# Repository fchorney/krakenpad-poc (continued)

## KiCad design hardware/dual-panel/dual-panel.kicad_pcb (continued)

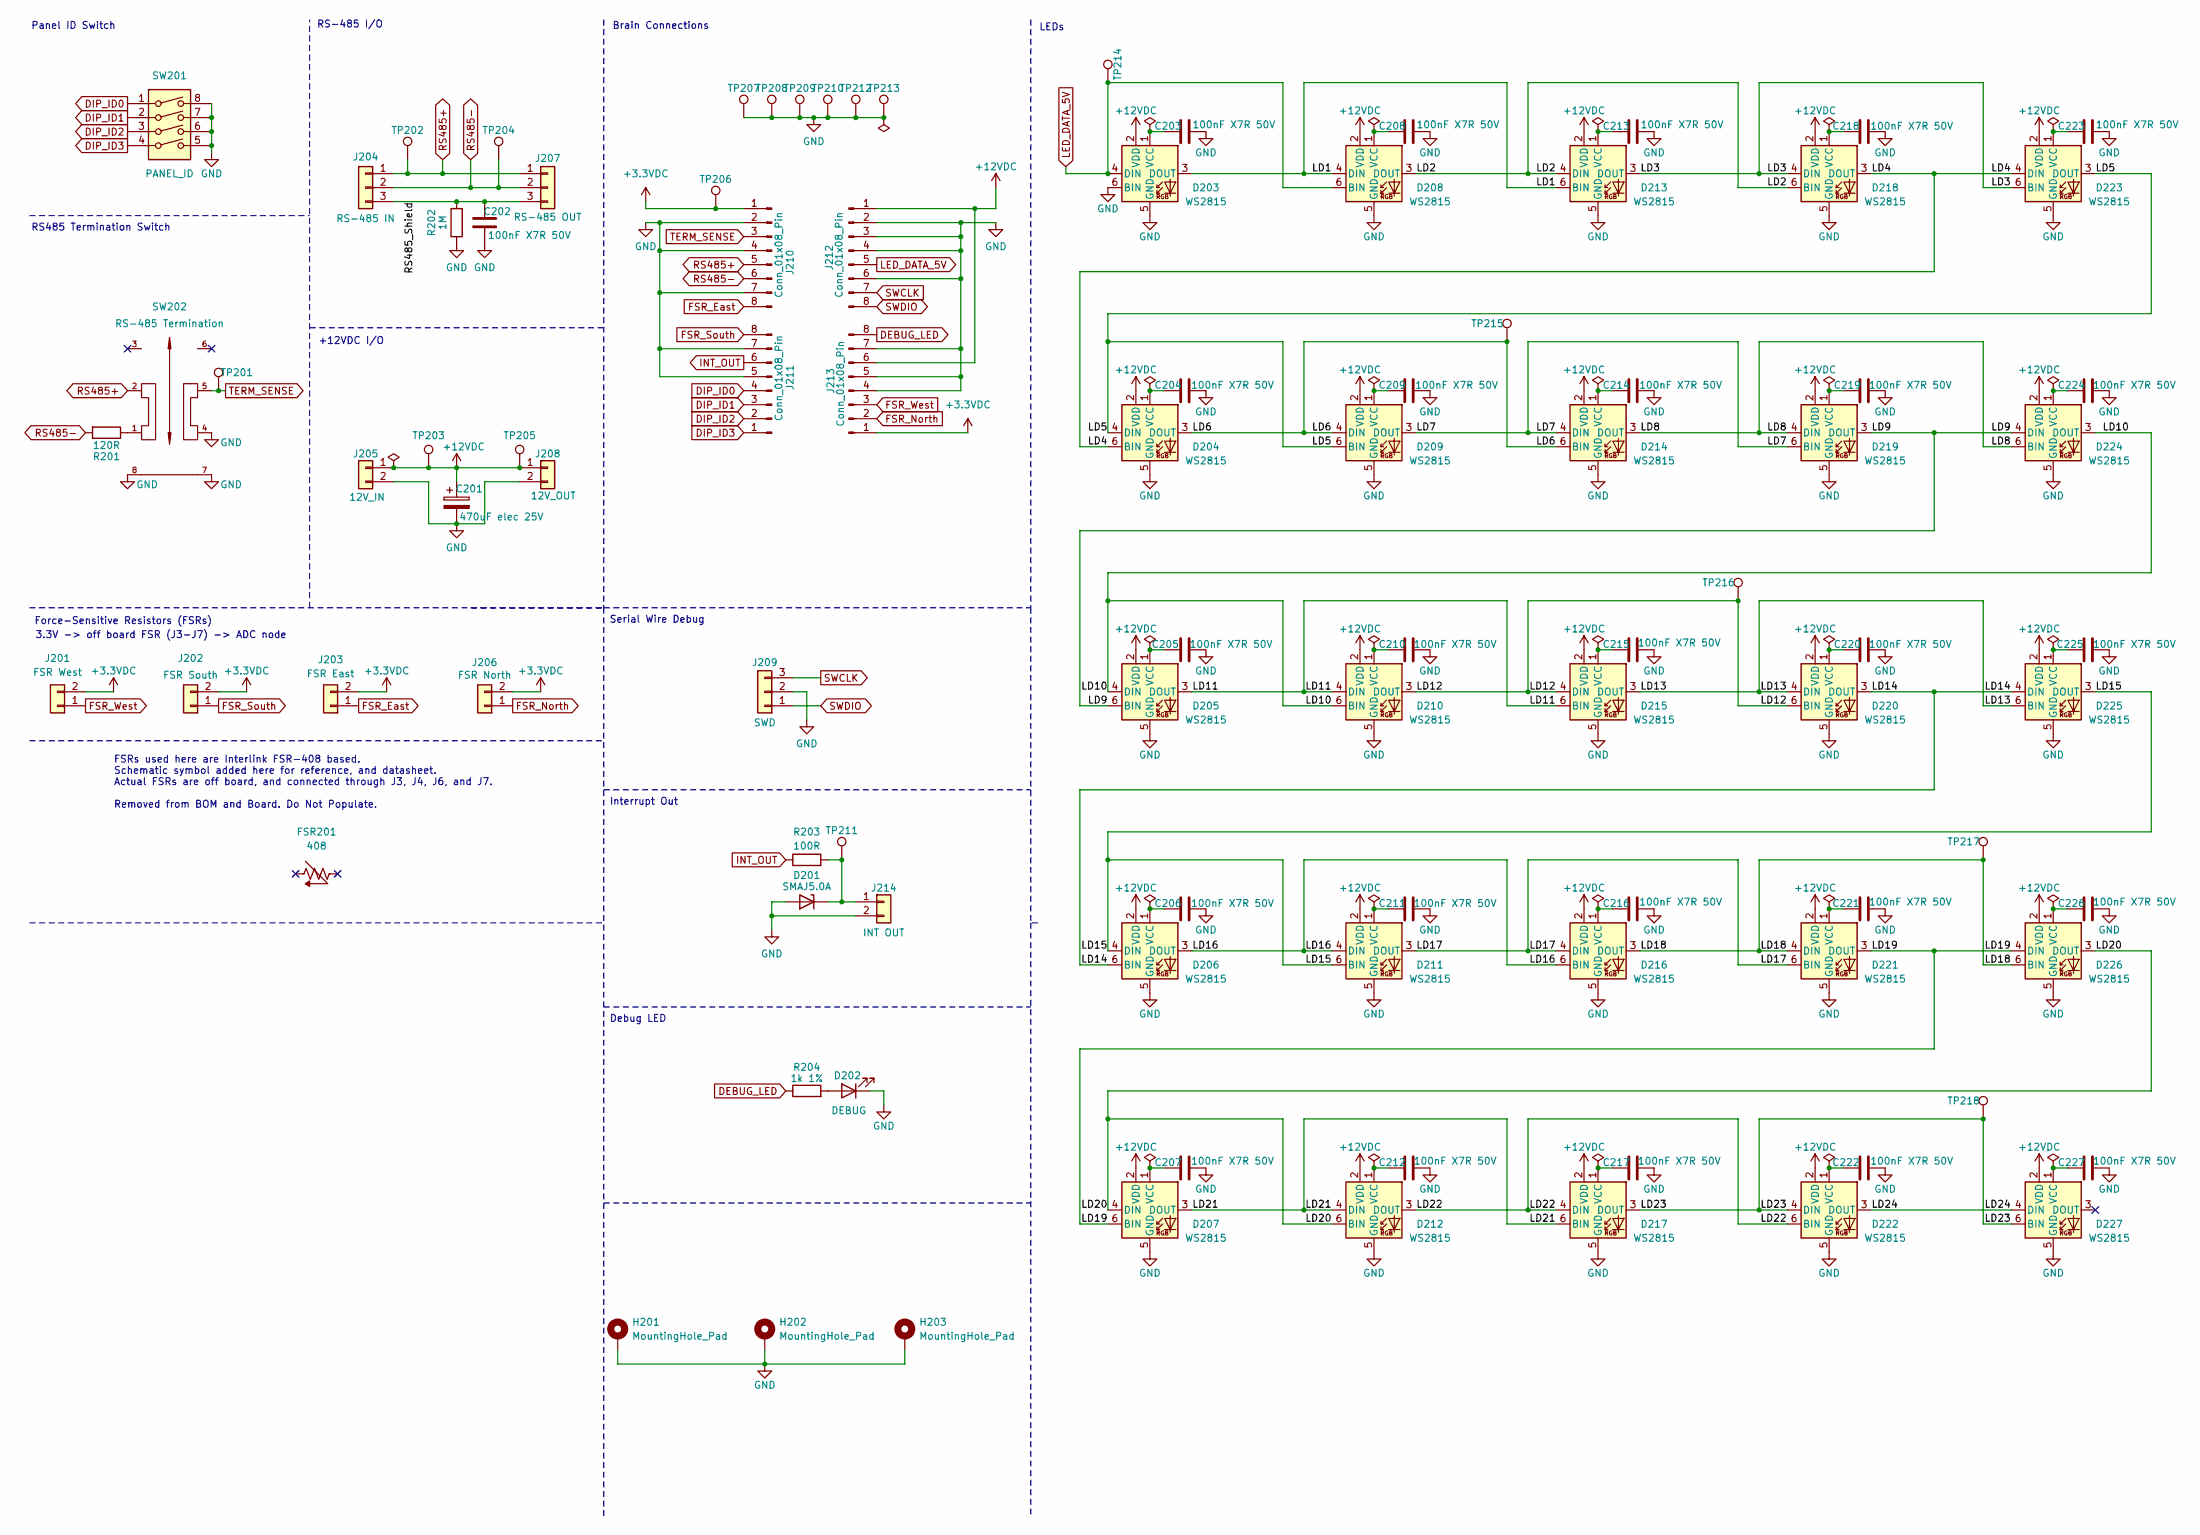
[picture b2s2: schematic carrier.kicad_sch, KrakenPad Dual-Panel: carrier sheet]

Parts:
C201: 470uF elec 25V; CP_Elec_10x10.5_RVT1E471M; MPN RVT1E471M1010; LCSC C82014
C202, C203, C204, C205, C206, C207, C208, C209, C210, C211, C212, C213, C214, C215, C216, C217, C218, C219, C220, C221, C222, C223, C224, C225, C226, C227: 100nF X7R 50V; C_0603_1608Metric; LCSC C14663
D201: SMAJ5.0A; D_SMA; MPN SMAJ5.0A; LCSC C113952
D202: DEBUG; LED_0603_1608Metric; MPN DYWH-19-21SUGC/4T; LCSC C47416536
D203, D204, D205, D206, D207, D208, D209, D210, D211, D212, D213, D214, D215, D216, D217, D218, D219, D220, D221, D222, D223, D224, D225, D226, D227: WS2815; WS2815_PLCC6_5.0x5.0mm_P1.6mm; MPN WS2815B-V1; LCSC C5446699
FSR201: 408
H201, H202, H203: MountingHole_Pad; MountingHole_3.2mm_M3_Pad
J201: FSR West; JST_PH_B2B-PH-K_1x02_P2.00mm_Vertical; MPN B2B-PH-K-S(LF)(SN); LCSC C131337
J202: FSR South; JST_PH_B2B-PH-K_1x02_P2.00mm_Vertical; MPN B2B-PH-K-S(LF)(SN); LCSC C131337
J203: FSR East; JST_PH_B2B-PH-K_1x02_P2.00mm_Vertical; MPN B2B-PH-K-S(LF)(SN); LCSC C131337
J204: RS-485 IN; Molex_Micro-Fit_3.0_43650-0300_1x03_P3.00mm_Horizontal; MPN 43650-0300; LCSC C503478
J205: 12V_IN; Molex_Micro-Fit_3.0_43650-0200_1x02_P3.00mm_Horizontal; MPN 43650-0200; LCSC C192562
J206: FSR North; JST_PH_B2B-PH-K_1x02_P2.00mm_Vertical; MPN B2B-PH-K-S(LF)(SN); LCSC C131337
J207: RS-485 OUT; Molex_Micro-Fit_3.0_43650-0300_1x03_P3.00mm_Horizontal; MPN 43650-0300; LCSC C503478
J208: 12V_OUT; Molex_Micro-Fit_3.0_43650-0200_1x02_P3.00mm_Horizontal; MPN 43650-0200; LCSC C192562
J209: SWD; PinHeader_1x03_P2.54mm_Vertical; MPN PZ254V-11-03P; LCSC C2937625
J210, J211, J212, J213: Conn_01x08_Pin; PinHeader_1x08_P2.54mm_Vertical
J214: INT OUT; TerminalBlock_WJ500V-5.08-2P; MPN WJ500V-5.08-2P; LCSC C8465
R201: 120R; R_0603_1608Metric; LCSC C22787
R202: 1M; R_0603_1608Metric; LCSC C22935
R203: 100R; R_0603_1608Metric; LCSC C22775
R204: 1k 1%; R_0603_1608Metric; LCSC C2907002
SW201: PANEL_ID; SW_DIP_SPSTx04_Slide_9.78x12.34mm_W7.62mm_P2.54mm; MPN DS-04; LCSC C52177925
SW202: RS-485 Termination; SW_SS22E01L5; MPN SS22E01L5; LCSC C609835
TP201, TP203, TP205: +12VDC; TestPoint_THTPad_D2.0mm_Drill1.0mm
TP202, TP204, TP206, TP207, TP208, TP209, TP210, TP211, TP212, TP213, TP215, TP216, TP217, TP218: GND; TestPoint_THTPad_D2.0mm_Drill1.0mm
TP214: LED Data 5.0V; TestPoint_THTPad_D2.0mm_Drill1.0mm

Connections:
+3.3VDC: J201.2, J202.2, J203.2, J206.2, J210.1, J213.1, TP206.1 (1_1); also elsewhere on the board
+12VDC: C201.1, D203.2 (VDD), D204.2 (VDD), D205.2 (VDD), D206.2 (VDD), D207.2 (VDD), D208.2 (VDD), D209.2 (VDD), D210.2 (VDD), D211.2 (VDD), D212.2 (VDD), D213.2 (VDD), D214.2 (VDD), D215.2 (VDD), D216.2 (VDD), D217.2 (VDD), D218.2 (VDD), D219.2 (VDD), D220.2 (VDD), D221.2 (VDD), D222.2 (VDD), D223.2 (VDD), D224.2 (VDD), D225.2 (VDD), D226.2 (VDD), D227.2 (VDD), J205.1, J208.1, J212.1, J213.6, TP203.1 (1_1), TP205.1 (1_1); also elsewhere on the board
/carrier/LD1: D203.3 (DOUT), D208.4 (DIN), D213.6 (BIN)
/carrier/LD2: D208.3 (DOUT), D213.4 (DIN), D218.6 (BIN)
/carrier/LD3: D213.3 (DOUT), D218.4 (DIN), D223.6 (BIN)
/carrier/LD4: D204.6 (BIN), D218.3 (DOUT), D223.4 (DIN)
/carrier/LD5: D204.4 (DIN), D209.6 (BIN), D223.3 (DOUT)
/carrier/LD6: D204.3 (DOUT), D209.4 (DIN), D214.6 (BIN), TP215.1 (1_1)
/carrier/LD7: D209.3 (DOUT), D214.4 (DIN), D219.6 (BIN)
/carrier/LD8: D214.3 (DOUT), D219.4 (DIN), D224.6 (BIN)
/carrier/LD9: D205.6 (BIN), D219.3 (DOUT), D224.4 (DIN)
/carrier/LD10: D205.4 (DIN), D210.6 (BIN), D224.3 (DOUT)
/carrier/LD11: D205.3 (DOUT), D210.4 (DIN), D215.6 (BIN)
/carrier/LD12: D210.3 (DOUT), D215.4 (DIN), D220.6 (BIN), TP216.1 (1_1)
/carrier/LD13: D215.3 (DOUT), D220.4 (DIN), D225.6 (BIN)
/carrier/LD14: D206.6 (BIN), D220.3 (DOUT), D225.4 (DIN)
/carrier/LD15: D206.4 (DIN), D211.6 (BIN), D225.3 (DOUT)
/carrier/LD16: D206.3 (DOUT), D211.4 (DIN), D216.6 (BIN)
/carrier/LD17: D211.3 (DOUT), D216.4 (DIN), D221.6 (BIN)
/carrier/LD18: D216.3 (DOUT), D221.4 (DIN), D226.6 (BIN), TP217.1 (1_1)
/carrier/LD19: D207.6 (BIN), D221.3 (DOUT), D226.4 (DIN)
/carrier/LD20: D207.4 (DIN), D212.6 (BIN), D226.3 (DOUT)
/carrier/LD21: D207.3 (DOUT), D212.4 (DIN), D217.6 (BIN)
/carrier/LD22: D212.3 (DOUT), D217.4 (DIN), D222.6 (BIN)
/carrier/LD23: D217.3 (DOUT), D222.4 (DIN), D227.6 (BIN), TP218.1 (1_1)
/carrier/LD24: D222.3 (DOUT), D227.4 (DIN)
/carrier/RS485_Shield: C202.2, J204.3, J207.3, R202.2
DEBUG_LED: J213.8, R204.1; also elsewhere on the board
DIP_ID0: J211.4, SW201.1; also elsewhere on the board
DIP_ID1: J211.3, SW201.2; also elsewhere on the board
DIP_ID2: J211.2, SW201.3; also elsewhere on the board
DIP_ID3: J211.1, SW201.4; also elsewhere on the board
FSR_East: J203.1, J210.8; also elsewhere on the board
FSR_North: J206.1, J213.2; also elsewhere on the board
FSR_South: J202.1, J211.8; also elsewhere on the board
FSR_West: J201.1, J213.3; also elsewhere on the board
GND: C201.2, C202.1, C203.2, C204.2, C205.2, C206.2, C207.2, C208.2, C209.2, C210.2, C211.2, C212.2, C213.2, C214.2, C215.2, C216.2, C217.2, C218.2, C219.2, C220.2, C221.2, C222.2, C223.2, C224.2, C225.2, C226.2, C227.2, D201.2 (A), D202.1 (K), D203.5 (GND), D203.6 (BIN), D204.5 (GND), D205.5 (GND), D206.5 (GND), D207.5 (GND), D208.5 (GND), D209.5 (GND), D210.5 (GND), D211.5 (GND), D212.5 (GND), D213.5 (GND), D214.5 (GND), D215.5 (GND), D216.5 (GND), D217.5 (GND), D218.5 (GND), D219.5 (GND), D220.5 (GND), D221.5 (GND), D222.5 (GND), D223.5 (GND), D224.5 (GND), D225.5 (GND), D226.5 (GND), D227.5 (GND), H201.1 (1_1), H202.1 (1_1), H203.1 (1_1), J205.2, J208.2, J209.2, J210.2, J210.4, J210.7, J211.5, J211.7, J212.2, J212.3, J212.4, J212.6, J213.4, J213.5, J213.7, J214.2, R202.1, SW201.5, SW201.6, SW201.7, SW201.8, SW202.4, SW202.7, SW202.8, TP207.1 (1_1), TP208.1 (1_1), TP209.1 (1_1), TP210.1 (1_1), TP212.1 (1_1), TP213.1 (1_1); also elsewhere on the board
INT_OUT: J211.6, R203.1; also elsewhere on the board
LED_DATA_5V: D203.4 (DIN), D208.6 (BIN), J212.5, TP214.1 (1_1); also elsewhere on the board
unnamed: D201.1 (K), J214.1, R203.2, TP211.1 (1_1)
unnamed: D202.2 (A), R204.2
unnamed: C203.1, D203.1 (VCC)
unnamed: C204.1, D204.1 (VCC)
unnamed: C205.1, D205.1 (VCC)
unnamed: C206.1, D206.1 (VCC)
unnamed: C207.1, D207.1 (VCC)
unnamed: C208.1, D208.1 (VCC)
unnamed: C209.1, D209.1 (VCC)
unnamed: C210.1, D210.1 (VCC)
unnamed: C211.1, D211.1 (VCC)
unnamed: C212.1, D212.1 (VCC)
unnamed: C213.1, D213.1 (VCC)
unnamed: C214.1, D214.1 (VCC)
unnamed: C215.1, D215.1 (VCC)
unnamed: C216.1, D216.1 (VCC)
unnamed: C217.1, D217.1 (VCC)
unnamed: C218.1, D218.1 (VCC)
unnamed: C219.1, D219.1 (VCC)
unnamed: C220.1, D220.1 (VCC)
unnamed: C221.1, D221.1 (VCC)
unnamed: C222.1, D222.1 (VCC)
unnamed: C223.1, D223.1 (VCC)
unnamed: C224.1, D224.1 (VCC)
unnamed: C225.1, D225.1 (VCC)
unnamed: C226.1, D226.1 (VCC)
unnamed: C227.1, D227.1 (VCC)
unnamed: R201.1, SW202.1
RS485+: J204.1, J207.1, J210.5, SW202.2, TP202.1 (1_1); also elsewhere on the board
RS485-: J204.2, J207.2, J210.6, R201.2, TP204.1 (1_1); also elsewhere on the board
SWCLK: J209.3, J212.7; also elsewhere on the board
SWDIO: J209.1, J212.8; also elsewhere on the board
TERM_SENSE: J210.3, SW202.5, TP201.1 (1_1); also elsewhere on the board

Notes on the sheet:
+12VDC I/O
Panel ID Switch
RS485 Termination Switch
Debug LED
Brain Connections
3.3V -> off board FSR (J3-J7) -> ADC node
LEDs
RS-485 I/O
Force-Sensitive Resistors (FSRs)
Interrupt Out
FSRs used here are Interlink FSR-408 based. Schematic symbol added here for reference, and datasheet. Actual FSRs are off board, and connected through J3, J4, J6, and J7. Removed from BOM and Board. Do Not Populate.
Serial Wire Debug

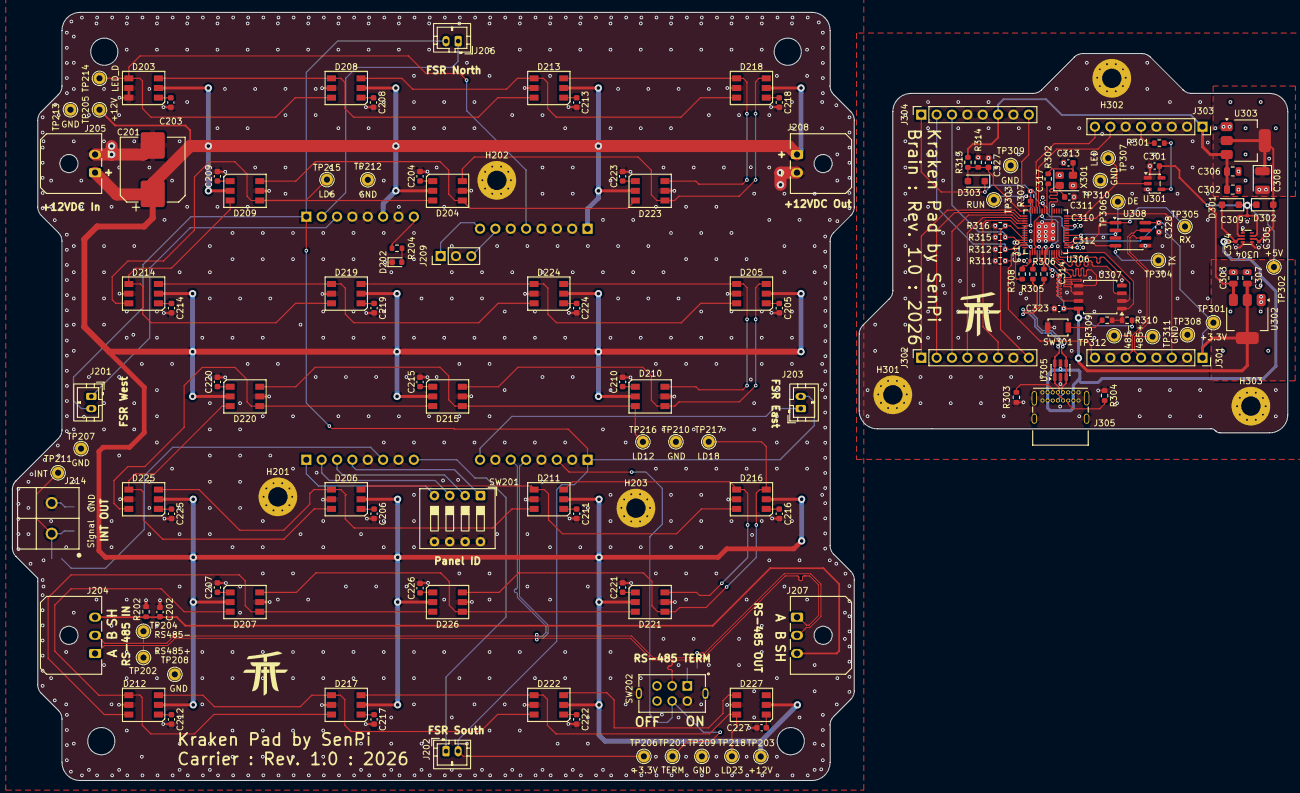
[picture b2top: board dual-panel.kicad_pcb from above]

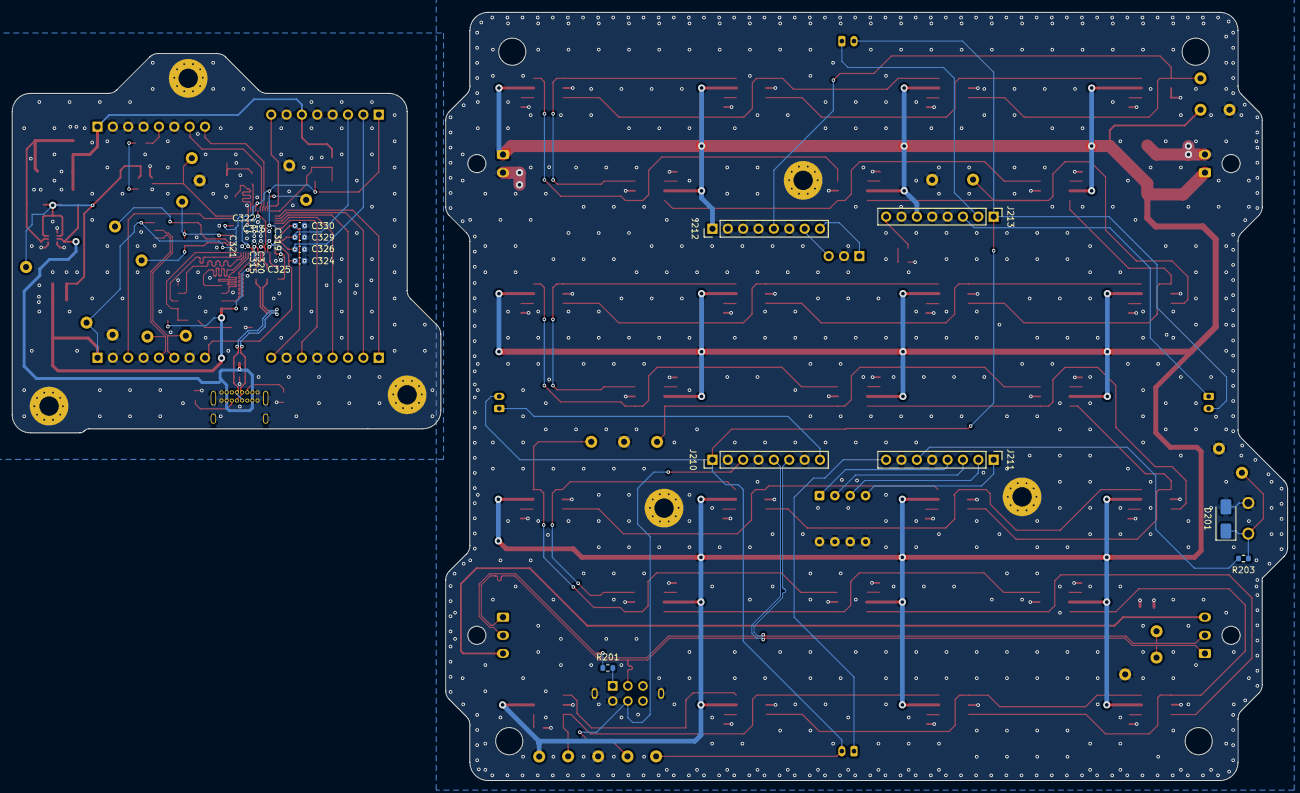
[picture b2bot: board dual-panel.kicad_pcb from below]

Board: 4 copper layers, 210.9 x 127.0 mm, 174 parts (18 on the bottom side), 100 nets.

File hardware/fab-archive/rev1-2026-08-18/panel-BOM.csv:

Comment,Designator,Footprint,LCSC
100R,R203,R_0603_1608Metric,C22775
100k,R313,R_0603_1608Metric,C25803
100nF X7R 50V,"C309,C310,C312,C314,C315,C316,C317,C321,C322,C325",C_0402_1005Metric_SilkTrim,C307331
100nF X7R 50V,"C202,C203,C204,C205,C206,C207,C208,C209,C210,C211,C212,C213,C214,C215,C216,C217,C218,C219,C220,C221,C222,C223,C224,C225,C226,C227,C301,C323,C327,C328",C_0603_1608Metric,C14663
10k,"R307,R310",R_0603_1608Metric,C2906982
10k 1%,"R311,R312,R315,R316",R_0603_1608Metric,C98220
10nF C0G 25V,"C324,C326,C329,C330",C_0603_1608Metric,C723749
10uF X5R 50V,"C302,C303,C306,C307",C_0805_2012Metric,C440198
120R,R201,R_0603_1608Metric,C22787
12MHz ABM8-272-T3,X301,Crystal_SMD_3225-4Pin_3.2x2.5mm,C20625731
15pF C0G 50V,"C311,C313",C_0603_1608Metric,C1644
1M,R202,R_0603_1608Metric,C22935
1k 1%,"R204,R302,R309",R_0603_1608Metric,C2907002
1uF X5R 25V,"C304,C305,C319,C320",C_0402_1005Metric_SilkTrim,C52923
2.2uF X5R 16V,C318,C_0402_1005Metric_SilkTrim,C170151
200R 1%,R308,R_0603_1608Metric,C8218
22uF tant 16V,C308,CP_EIA-3528-21_Kemet-B,C8020
27R 1%,"R305,R306",R_0603_1608Metric,C25190
330R,R301,R_0603_1608Metric,C23138
33k,R314,R_0603_1608Metric,C4216
470uF elec 25V,C201,CP_Elec_10x10.5_RVT1E471M,C82014
5.1k,"R303,R304",R_0603_1608Metric,C23186
AMS1117-5.0,U303,SOT-223-3_TabPin2,C6187
AP7361C-33ER-13,U302,SOT-223-3_TabPin2,C3743528
BOOTSEL,SW301,SW_SPST_B3U-1000P,C231329
DEBUG,D202,LED_0603_1608Metric,C47416536
LM66200,U304,SOT-583-8,C3235556
PMEG3015EH,D303,D_SOD-123F,C552867
RP2040,U306,QFN-56-1EP_7x7mm_P0.4mm_EP3.2x3.2mm_RPiPad,C2040
SMAJ5.0A,D201,D_SMA,C113952
SN74AHCT1G125,U301,SOT-23-5,C7484
THVD1450,U308,SOIC-8_3.9x4.9mm_P1.27mm,C2671361
USBLC6-2SC6,U305,SOT-23-6,C2827654
W25Q32JV,U307,SOIC-8_5.3x5.3mm_P1.27mm,C179173
WS2815,"D203,D204,D205,D206,D207,D208,D209,D210,D211,D212,D213,D214,D215,D216,D217,D218,D219,D220,D221,D222,D223,D224,D225,D226,D227",WS2815_PLCC6_5.0x5.0mm_P1.6mm,C5446699

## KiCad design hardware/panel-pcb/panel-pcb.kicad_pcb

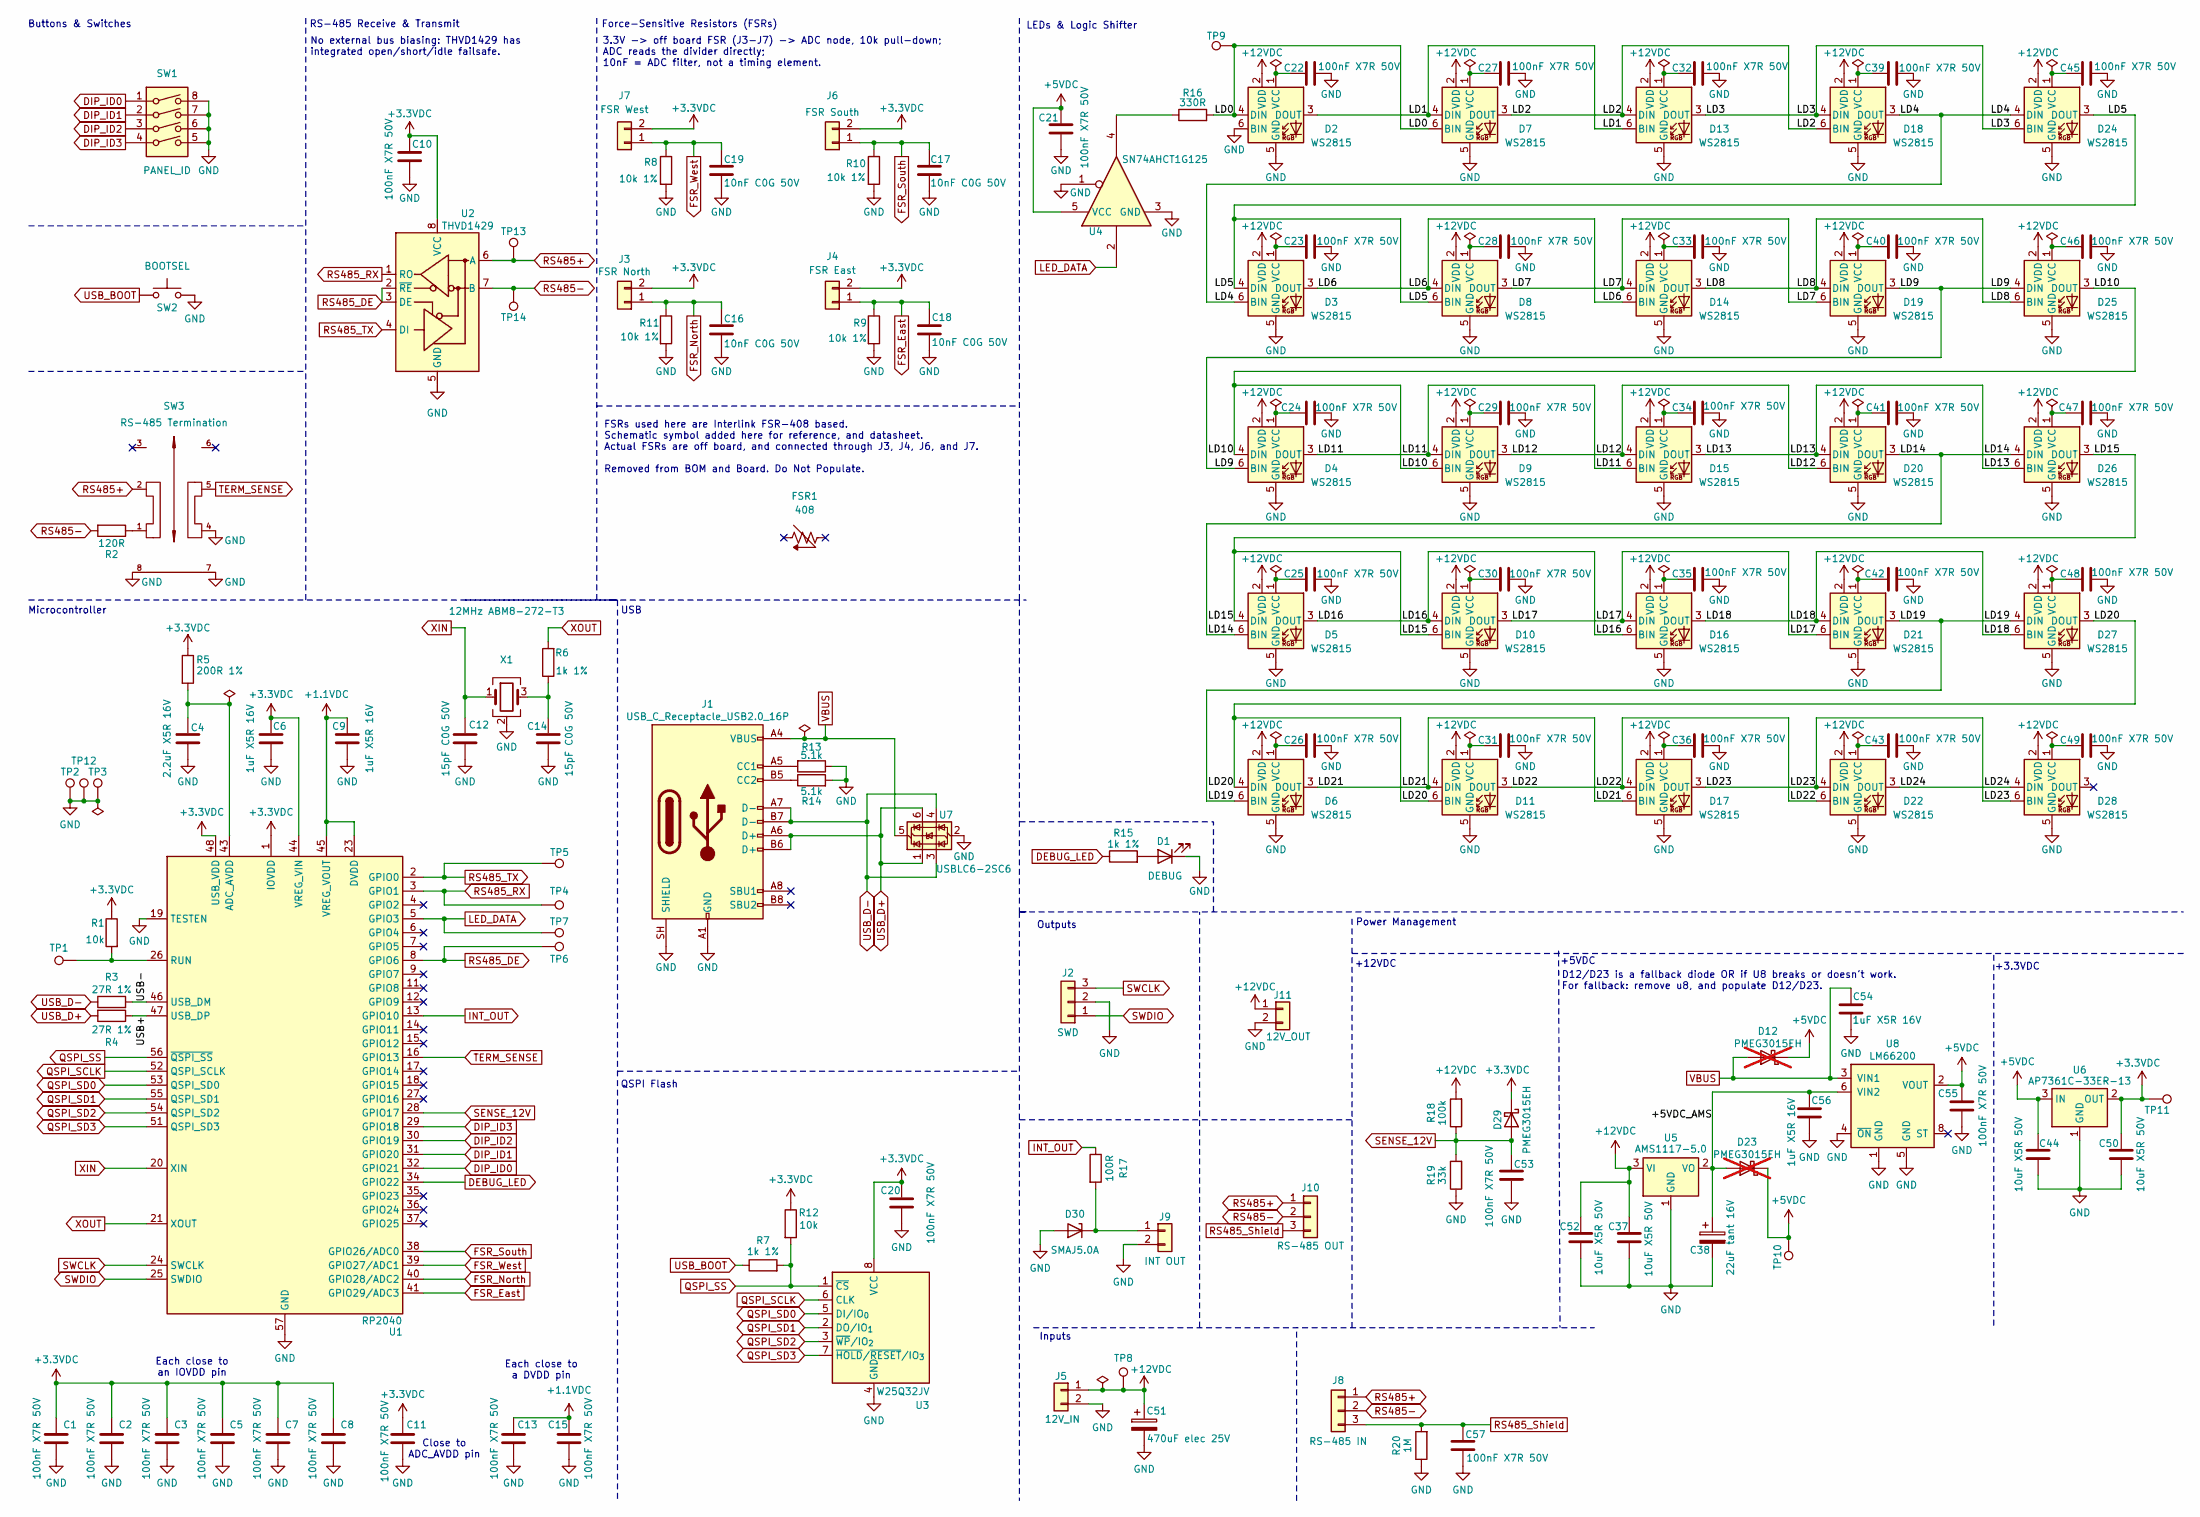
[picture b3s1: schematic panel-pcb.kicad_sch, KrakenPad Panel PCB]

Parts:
C1, C2, C3, C5, C7, C8, C11, C13, C15, C55: 100nF X7R 50V; C_0402_1005Metric_SilkTrim; LCSC C307331
C4: 2.2uF X5R 16V; C_0402_1005Metric_SilkTrim; LCSC C170151
C6, C9, C54, C56: 1uF X5R 16V; C_0402_1005Metric_SilkTrim; LCSC C52923
C10, C20, C21, C22, C23, C24, C25, C26, C27, C28, C29, C30, C31, C32, C33, C34, C35, C36, C39, C40, C41, C42, C43, C45, C46, C47, C48, C49, C53, C57: 100nF X7R 50V; C_0603_1608Metric; LCSC C14663
C12, C14: 15pF C0G 50V; C_0603_1608Metric; LCSC C1644
C16, C17, C18, C19: 10nF C0G 50V; C_0603_1608Metric; LCSC C57112
C37, C44, C50, C52: 10uF X5R 50V; C_0805_2012Metric; LCSC C440198
C38: 22uF tant 16V; CP_EIA-3528-21_Kemet-B; MPN TAJB226K016RNJ; LCSC C8020
C51: 470uF elec 25V; CP_Elec_10x10.5_RVT1E471M; MPN RVT1E471M1010; LCSC C82014
D1: DEBUG; LED_0603_1608Metric; MPN DYWH-19-21SUGC/4T; LCSC C47416536
D2, D3, D4, D5, D6, D7, D8, D9, D10, D11, D13, D14, D15, D16, D17, D18, D19, D20, D21, D22, D24, D25, D26, D27, D28: WS2815; WS2815_PLCC6_5.0x5.0mm_P1.6mm; MPN WS2815B-V1; LCSC C5446699
D12, D23: PMEG3015EH; D_SOD-123F; MPN PMEG3015EH,115; LCSC C552867; not fitted
D29: PMEG3015EH; D_SOD-123F; MPN PMEG3015EH,115; LCSC C552867
D30: SMAJ5.0A; D_SMA; MPN SMAJ5.0A; LCSC C113952
FSR1: 408
J1: USB_C_Receptacle_USB2.0_16P; USB_C_Receptacle_LCK_TCF829D_TEMPLATE; MPN LCK-TCF829D; LCSC C53184807
J2: SWD; PinHeader_1x03_P2.54mm_Vertical; MPN PZ254V-11-03P; LCSC C2937625
J3: FSR North; JST_PH_B2B-PH-K_1x02_P2.00mm_Vertical; MPN B2B-PH-K-S(LF)(SN); LCSC C131337
J4: FSR East; JST_PH_B2B-PH-K_1x02_P2.00mm_Vertical; MPN B2B-PH-K-S(LF)(SN); LCSC C131337
J5: 12V_IN; Molex_Micro-Fit_3.0_43650-0200_1x02_P3.00mm_Horizontal; MPN 43650-0200; LCSC C192562
J6: FSR South; JST_PH_B2B-PH-K_1x02_P2.00mm_Vertical; MPN B2B-PH-K-S(LF)(SN); LCSC C131337
J7: FSR West; JST_PH_B2B-PH-K_1x02_P2.00mm_Vertical; MPN B2B-PH-K-S(LF)(SN); LCSC C131337
J8: RS-485 IN; Molex_Micro-Fit_3.0_43650-0300_1x03_P3.00mm_Horizontal; MPN 43650-0300; LCSC C503478
J9: INT OUT; TerminalBlock_WJ500V-5.08-2P; MPN WJ500V-5.08-2P; LCSC C8465
J10: RS-485 OUT; Molex_Micro-Fit_3.0_43650-0300_1x03_P3.00mm_Horizontal; MPN 43650-0300; LCSC C503478
J11: 12V_OUT; Molex_Micro-Fit_3.0_43650-0200_1x02_P3.00mm_Horizontal; MPN 43650-0200; LCSC C192562
R1, R12: 10k; R_0603_1608Metric; LCSC C2906982
R2: 120R; R_0603_1608Metric; LCSC C22787
R3, R4: 27R 1%; R_0603_1608Metric; LCSC C858950
R5: 200R 1%; R_0603_1608Metric; LCSC C8218
R6, R7, R15: 1k 1%; R_0603_1608Metric; LCSC C2907002
R8, R9, R10, R11: 10k 1%; R_0603_1608Metric; LCSC C98220
R13, R14: 5.1k; R_0603_1608Metric; LCSC C23186
R16: 330R; R_0603_1608Metric; LCSC C23138
R17: 100R; R_0603_1608Metric; LCSC C22775
R18: 100k; R_0603_1608Metric; LCSC C25803
R19: 33k; R_0603_1608Metric; LCSC C4216
R20: 1M; R_0603_1608Metric; LCSC C22935
SW1: PANEL_ID; SW_DIP_SPSTx04_Slide_9.78x12.34mm_W7.62mm_P2.54mm; MPN DS-04; LCSC C52177925
SW2: BOOTSEL; SW_SPST_B3U-1000P; MPN B3U-1000P; LCSC C231329
SW3: RS-485 Termination; SW_SS22E01L5; MPN SS22E01L5; LCSC C609835
TP1: RUN; TestPoint_THTPad_D2.0mm_Drill1.0mm
TP2, TP3, TP12: GND; TestPoint_THTPad_D2.0mm_Drill1.0mm
TP4: UART RX; TestPoint_THTPad_D2.0mm_Drill1.0mm
TP5: UART TX; TestPoint_THTPad_D2.0mm_Drill1.0mm
TP6: RS-485 DE; TestPoint_THTPad_D2.0mm_Drill1.0mm
TP7: LED Data 3.3V; TestPoint_THTPad_D2.0mm_Drill1.0mm
TP8: +12VDC; TestPoint_THTPad_D2.0mm_Drill1.0mm
TP9: LED Data 5.0V; TestPoint_THTPad_D2.0mm_Drill1.0mm
TP10: +5VDC; TestPoint_THTPad_D2.0mm_Drill1.0mm
TP11: +3.3VDC; TestPoint_THTPad_D2.0mm_Drill1.0mm
TP13: RS485+; TestPoint_THTPad_D2.0mm_Drill1.0mm
TP14: RS485-; TestPoint_THTPad_D2.0mm_Drill1.0mm
U1: RP2040; QFN-56-1EP_7x7mm_P0.4mm_EP3.2x3.2mm; MPN RP2040; LCSC C2040
U2: THVD1429; SOIC-8_3.9x4.9mm_P1.27mm; MPN THVD1429DR; LCSC C1850236
U3: W25Q32JV; SOIC-8_5.3x5.3mm_P1.27mm; MPN W25Q32JVSSIQ; LCSC C179173
U4: SN74AHCT1G125; SOT-23-5; MPN SN74AHCT1G125DBVR; LCSC C7484
U5: AMS1117-5.0; SOT-223-3_TabPin2; MPN AMS1117-5.0; LCSC C6187
U6: AP7361C-33ER-13; SOT-223-3_TabPin2; MPN AP7361C-33ER-13; LCSC C3743528
U7: USBLC6-2SC6; SOT-23-6; MPN USBLC6-2SC6; LCSC C2827654
U8: LM66200; SOT-583-8; MPN LM66200DRLR; LCSC C3235556
X1: 12MHz ABM8-272-T3; Crystal_SMD_3225-4Pin_3.2x2.5mm; MPN ABM8-272-T3; LCSC C20625731

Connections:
+1.1VDC: C9.1, C13.1, C15.1, U1.23 (DVDD), U1.45 (VREG_VOUT), U1.50 (DVDD)
+3.3VDC: C1.1, C2.1, C3.1, C5.1, C6.2, C7.1, C8.1, C10.1, C11.1, C20.1, C50.1, D29.1 (K), J3.2, J4.2, J6.2, J7.2, R1.1, R5.1, R12.1, TP11.1 (1_1), U1.1 (IOVDD), U1.10 (IOVDD), U1.22 (IOVDD), U1.33 (IOVDD), U1.42 (IOVDD), U1.44 (VREG_VIN), U1.48 (USB_VDD), U1.49 (IOVDD), U2.8 (VCC), U3.8 (VCC), U6.2 (OUT)
+5VDC: C21.1, C44.1, C55.1, D12.1 (K), D23.1 (K), TP10.1 (1_1), U4.5 (VCC), U6.3 (IN), U8.2 (VOUT), U8.7 (VOUT)
+12VDC: C37.1, C51.1, C52.1, D2.2 (VDD), D3.2 (VDD), D4.2 (VDD), D5.2 (VDD), D6.2 (VDD), D7.2 (VDD), D8.2 (VDD), D9.2 (VDD), D10.2 (VDD), D11.2 (VDD), D13.2 (VDD), D14.2 (VDD), D15.2 (VDD), D16.2 (VDD), D17.2 (VDD), D18.2 (VDD), D19.2 (VDD), D20.2 (VDD), D21.2 (VDD), D22.2 (VDD), D24.2 (VDD), D25.2 (VDD), D26.2 (VDD), D27.2 (VDD), D28.2 (VDD), J5.1, J11.1, R18.2, TP8.1 (1_1), U5.3 (VI)
/+5VDC_AMS: C38.1, C56.2, D23.2 (A), U5.2 (VO), U8.6 (VIN2)
/LD0: D2.4 (DIN), D7.6 (BIN), R16.2, TP9.1 (1_1)
/LD1: D2.3 (DOUT), D7.4 (DIN), D13.6 (BIN)
/LD2: D7.3 (DOUT), D13.4 (DIN), D18.6 (BIN)
/LD3: D13.3 (DOUT), D18.4 (DIN), D24.6 (BIN)
/LD4: D3.6 (BIN), D18.3 (DOUT), D24.4 (DIN)
/LD5: D3.4 (DIN), D8.6 (BIN), D24.3 (DOUT)
/LD6: D3.3 (DOUT), D8.4 (DIN), D14.6 (BIN)
/LD7: D8.3 (DOUT), D14.4 (DIN), D19.6 (BIN)
/LD8: D14.3 (DOUT), D19.4 (DIN), D25.6 (BIN)
/LD9: D4.6 (BIN), D19.3 (DOUT), D25.4 (DIN)
/LD10: D4.4 (DIN), D9.6 (BIN), D25.3 (DOUT)
/LD11: D4.3 (DOUT), D9.4 (DIN), D15.6 (BIN)
/LD12: D9.3 (DOUT), D15.4 (DIN), D20.6 (BIN)
/LD13: D15.3 (DOUT), D20.4 (DIN), D26.6 (BIN)
/LD14: D5.6 (BIN), D20.3 (DOUT), D26.4 (DIN)
/LD15: D5.4 (DIN), D10.6 (BIN), D26.3 (DOUT)
/LD16: D5.3 (DOUT), D10.4 (DIN), D16.6 (BIN)
/LD17: D10.3 (DOUT), D16.4 (DIN), D21.6 (BIN)
/LD18: D16.3 (DOUT), D21.4 (DIN), D27.6 (BIN)
/LD19: D6.6 (BIN), D21.3 (DOUT), D27.4 (DIN)
/LD20: D6.4 (DIN), D11.6 (BIN), D27.3 (DOUT)
/LD21: D6.3 (DOUT), D11.4 (DIN), D17.6 (BIN)
/LD22: D11.3 (DOUT), D17.4 (DIN), D22.6 (BIN)
/LD23: D17.3 (DOUT), D22.4 (DIN), D28.6 (BIN)
/LD24: D22.3 (DOUT), D28.4 (DIN)
/USB+: R4.1, U1.47 (USB_DP)
/USB-: R3.2, U1.46 (USB_DM)
DEBUG_LED: R15.1, U1.34 (GPIO22)
DIP_ID0: SW1.1, U1.32 (GPIO21)
DIP_ID1: SW1.2, U1.31 (GPIO20)
DIP_ID2: SW1.3, U1.30 (GPIO19)
DIP_ID3: SW1.4, U1.29 (GPIO18)
FSR_East: C18.1, J4.1, R9.1, U1.41 (GPIO29/ADC3)
FSR_North: C16.1, J3.1, R11.1, U1.40 (GPIO28/ADC2)
FSR_South: C17.1, J6.1, R10.1, U1.38 (GPIO26/ADC0)
FSR_West: C19.1, J7.1, R8.1, U1.39 (GPIO27/ADC1)
GND: C1.2, C2.2, C3.2, C4.1, C5.2, C6.1, C7.2, C8.2, C9.2, C10.2, C11.2, C12.2, C13.2, C14.2, C15.2, C16.2, C17.2, C18.2, C19.2, C20.2, C21.2, C22.2, C23.2, C24.2, C25.2, C26.2, C27.2, C28.2, C29.2, C30.2, C31.2, C32.2, C33.2, C34.2, C35.2, C36.2, C37.2, C38.2, C39.2, C40.2, C41.2, C42.2, C43.2, C44.2, C45.2, C46.2, C47.2, C48.2, C49.2, C50.2, C51.2, C52.2, C53.1, C54.1, C55.2, C56.1, C57.1, D1.1 (K), D2.5 (GND), D2.6 (BIN), D3.5 (GND), D4.5 (GND), D5.5 (GND), D6.5 (GND), D7.5 (GND), D8.5 (GND), D9.5 (GND), D10.5 (GND), D11.5 (GND), D13.5 (GND), D14.5 (GND), D15.5 (GND), D16.5 (GND), D17.5 (GND), D18.5 (GND), D19.5 (GND), D20.5 (GND), D21.5 (GND), D22.5 (GND), D24.5 (GND), D25.5 (GND), D26.5 (GND), D27.5 (GND), D28.5 (GND), D30.2 (A), J1.A1 (GND), J1.A12 (GND), J1.B1 (GND), J1.B12 (GND), J1.SH (SHIELD), J2.2, J5.2, J9.2, J11.2, R8.2, R9.2, R10.2, R11.2, R13.1, R14.2, R19.1, R20.1, SW1.5, SW1.6, SW1.7, SW1.8, SW2.2, SW3.4, SW3.7, SW3.8, TP2.1 (1_1), TP3.1 (1_1), TP12.1 (1_1), U1.19 (TESTEN), U1.57 (GND), U2.5 (GND), U3.4 (GND), U4.1, U4.3 (GND), U5.1 (GND), U6.1 (GND), U7.2 (GND), U8.1 (GND), U8.4 (~ON), U8.5 (GND), X1.2 (G), X1.4 (G)
INT_OUT: R17.1, U1.13 (GPIO10)
LED_DATA: TP7.1 (1_1), U1.5 (GPIO3), U4.2
unnamed: C14.1, R6.1, X1.3
unnamed: D1.2 (A), R15.2
unnamed: C22.1, D2.1 (VCC)
unnamed: C23.1, D3.1 (VCC)
unnamed: C24.1, D4.1 (VCC)
unnamed: C25.1, D5.1 (VCC)
unnamed: C26.1, D6.1 (VCC)
unnamed: C27.1, D7.1 (VCC)
unnamed: C28.1, D8.1 (VCC)
unnamed: C29.1, D9.1 (VCC)
unnamed: C30.1, D10.1 (VCC)
unnamed: C31.1, D11.1 (VCC)
unnamed: C32.1, D13.1 (VCC)
unnamed: C33.1, D14.1 (VCC)
unnamed: C34.1, D15.1 (VCC)
unnamed: C35.1, D16.1 (VCC)
unnamed: C36.1, D17.1 (VCC)
unnamed: C39.1, D18.1 (VCC)
unnamed: C40.1, D19.1 (VCC)
unnamed: C41.1, D20.1 (VCC)
unnamed: C42.1, D21.1 (VCC)
unnamed: C43.1, D22.1 (VCC)
unnamed: C45.1, D24.1 (VCC)
unnamed: C46.1, D25.1 (VCC)
unnamed: C47.1, D26.1 (VCC)
unnamed: C48.1, D27.1 (VCC)
unnamed: C49.1, D28.1 (VCC)
unnamed: D30.1 (K), J9.1, R17.2
unnamed: J1.A5 (CC1), R13.2
unnamed: J1.B5 (CC2), R14.1
unnamed: R2.1, SW3.1
unnamed: R16.1, U4.4
unnamed: C4.2, R5.2, U1.43 (ADC_AVDD)
unnamed: R1.2, TP1.1 (1_1), U1.26 (RUN)
QSPI_SCLK: U1.52 (QSPI_SCLK), U3.6 (CLK)
QSPI_SD0: U1.53 (QSPI_SD0), U3.5 (DI/IO_{0})
QSPI_SD1: U1.55 (QSPI_SD1), U3.2 (DO/IO_{1})
QSPI_SD2: U1.54 (QSPI_SD2), U3.3 (~WP/IO_{2})
QSPI_SD3: U1.51 (QSPI_SD3), U3.7 (~HOLD/~RESET/IO_{3})
QSPI_SS: R7.2, R12.2, U1.56 (~QSPI_SS), U3.1 (~CS)
RS485+: J8.1, J10.1, SW3.2, TP13.1 (1_1), U2.6 (A)
RS485-: J8.2, J10.2, R2.2, TP14.1 (1_1), U2.7 (B)
RS485_DE: TP6.1 (1_1), U1.8 (GPIO6), U2.2 (~RE), U2.3 (DE)
RS485_RX: TP4.1 (1_1), U1.3 (GPIO1), U2.1 (RO)
RS485_Shield: C57.2, J8.3, J10.3, R20.2
RS485_TX: TP5.1 (1_1), U1.2 (GPIO0), U2.4 (DI)
SENSE_12V: C53.2, D29.2 (A), R18.1, R19.2, U1.28 (GPIO17)
SWCLK: J2.3, U1.24 (SWCLK)
SWDIO: J2.1, U1.25 (SWDIO)
TERM_SENSE: SW3.5, U1.16 (GPIO13)
USB_BOOT: R7.1, SW2.1
USB_D+: J1.A6 (D+), J1.B6 (D+), R4.2, U7.1 (I/O1), U7.6 (I/O1)
USB_D-: J1.A7 (D-), J1.B7 (D-), R3.1, U7.3 (I/O2), U7.4 (I/O2)
VBUS: C54.2, D12.2 (A), J1.A4 (VBUS), J1.A9 (VBUS), J1.B4 (VBUS), J1.B9 (VBUS), U7.5 (VBUS), U8.3 (VIN1)
XIN: C12.1, U1.20 (XIN), X1.1
XOUT: R6.2, U1.21 (XOUT)

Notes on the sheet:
QSPI Flash
+5VDC
Each close to an IOVDD pin
Inputs
Close to ADC_AVDD pin
Buttons & Switches
Power Management
Outputs
D12/D23 is a fallback diode OR if U8 breaks or doesn't work. For fallback: remove u8, and populate D12/D23.
Each close to a DVDD pin
Microcontroller
USB
3.3V -> off board FSR (J3-J7) -> ADC node, 10k pull-down; ADC reads the divider directly; 10nF = ADC filter, not a timing element.
LEDs & Logic Shifter
Force-Sensitive Resistors (FSRs)
+3.3VDC
FSRs used here are Interlink FSR-408 based. Schematic symbol added here for reference, and datasheet. Actual FSRs are off board, and connected through J3, J4, J6, and J7. Removed from BOM and Board. Do Not Populate.
+12VDC
RS-485 Receive & Transmit
No external bus biasing: THVD1429 has integrated open/short/idle failsafe.
